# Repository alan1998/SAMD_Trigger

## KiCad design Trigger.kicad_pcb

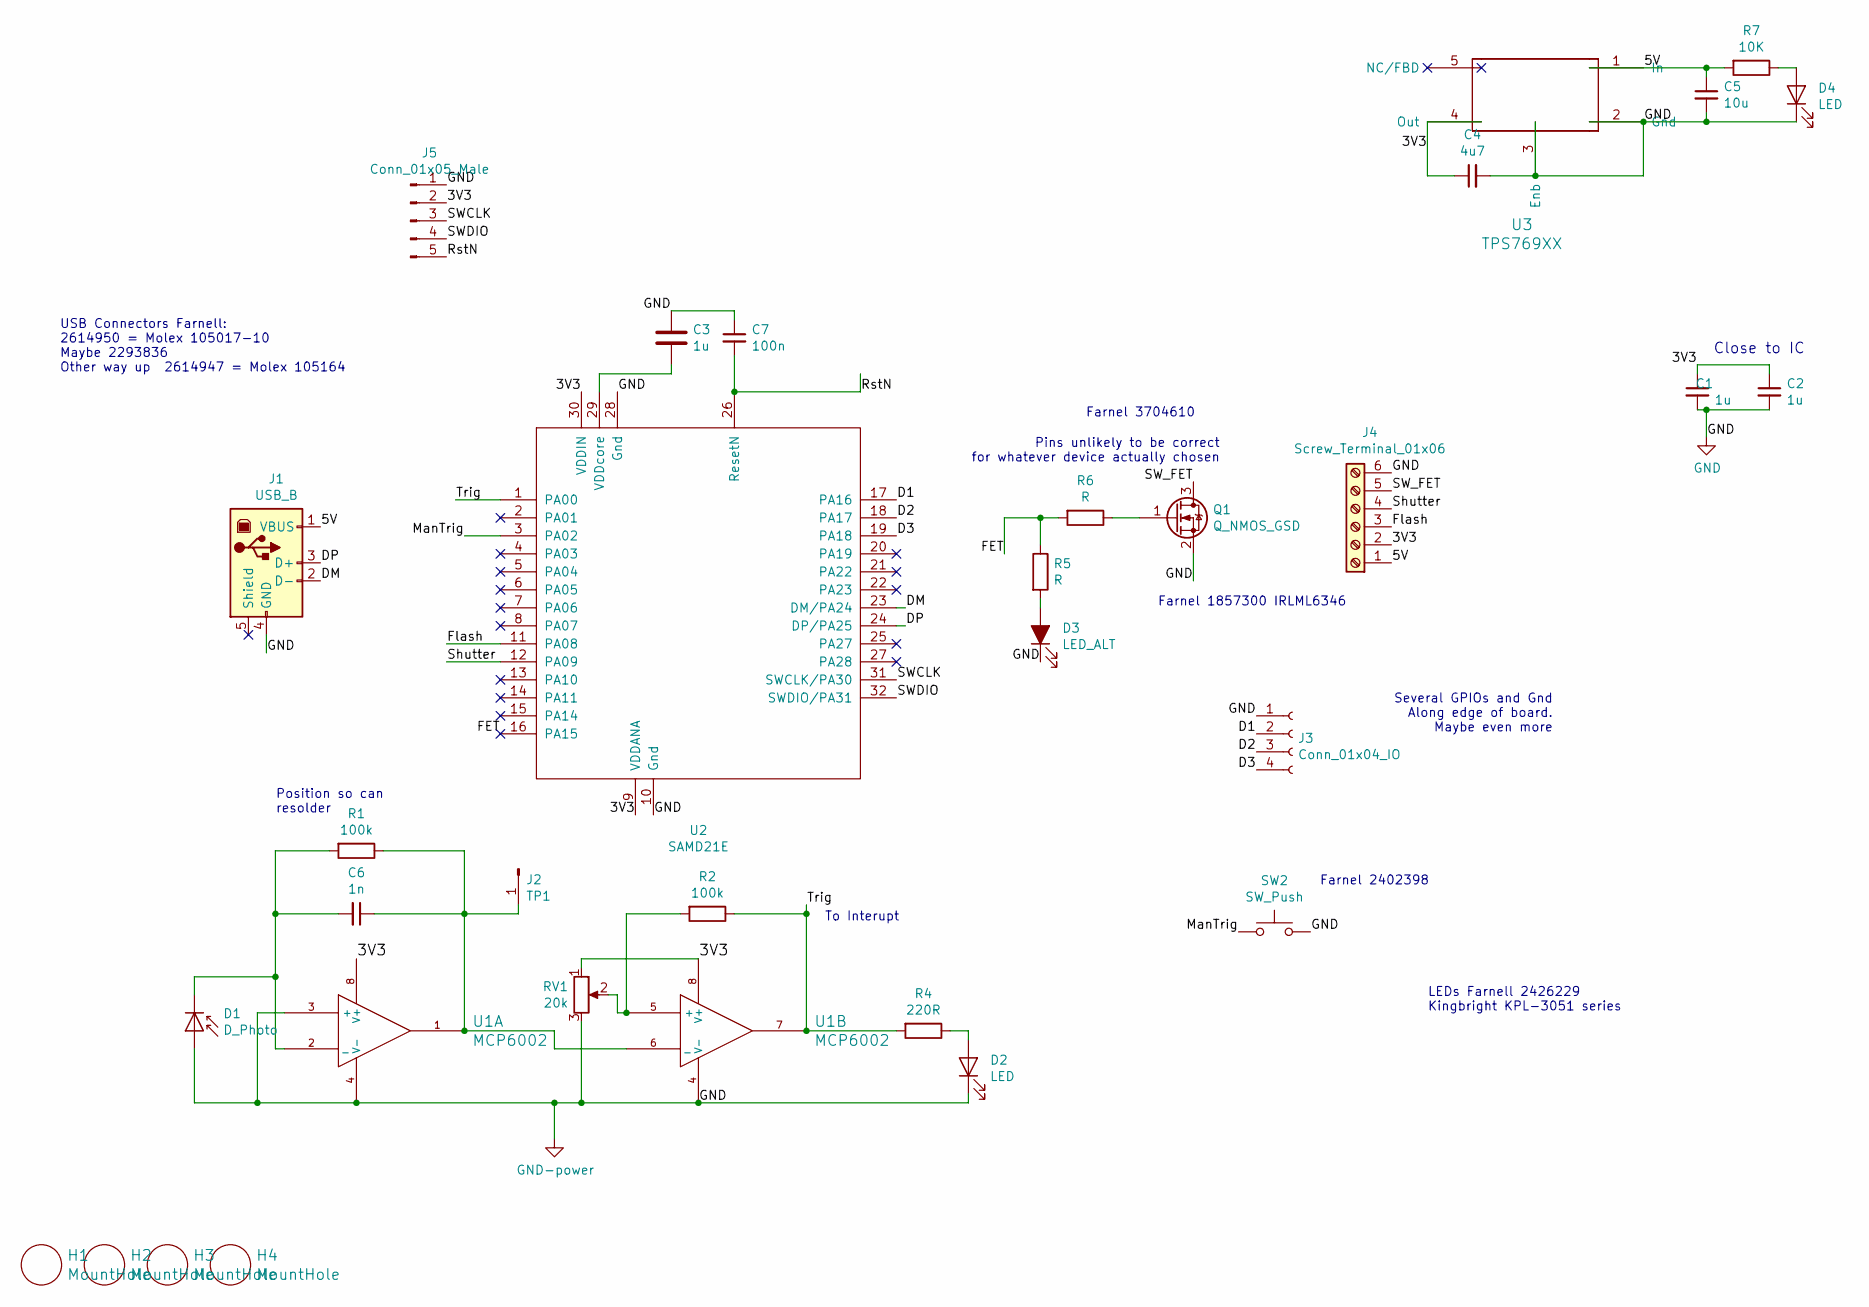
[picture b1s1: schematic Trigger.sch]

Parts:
C1, C2, C3: 1u; C_0805_HandSoldering
C4: 4u7; C_0805_HandSoldering
C5: 10u; C_0805_HandSoldering
C6: 1n; C_0805_HandSoldering
C7: 100n; C_0805_HandSoldering
D1: D_Photo; Pin_Header_Straight_1x02
D2, D4: LED; LED_SMD_3015
D3: LED_ALT; LED_SMD_3015
H1, H2, H3, H4: MountHole; 3mm_mount
J1: USB_B; USB_B_Micro_47346-0001
J2: TP1; Pin_Header_Angled_1x01
J3: Conn_01x04_IO; Pin_Header_Straight_1x04
J4: Screw_Terminal_01x06; Screw_6way_3_5mm
J5: Conn_01x05_Male; Pin_Header_Straight_1x05
Q1: Q_NMOS_GSD; SOT-23
R1: 100k; R_0805_HandSoldering
R2: 100k; R_0805
R4: 220R; R_0805
R5, R6: R; R_0805
R7: 10K; R_0805
RV1: 20k; Potentiometer_WirePads_largePads
SW2: SW_Push; Tact_SW
U1: MCP6002; SOIC-8-N
U2: SAMD21E; TQFP-32_7x7mm_Pitch0.8mm
U3: TPS769XX; SOT23_(DBV)

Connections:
/3V3: C1.1, C2.1, C4.1, J4.2, J5.2, RV1.1, U1.8 (V+), U2.9 (VDDANA), U2.30 (VDDIN), U3.4 (Out)
/5V: C5.1, J1.1 (VBUS), J4.1, R7.2, U3.1 (In)
/D1: J3.2, U2.17 (PA16)
/D2: J3.3, U2.18 (PA17)
/D3: J3.4, U2.19 (PA18)
/DM: J1.2 (D-), U2.23 (DM/PA24)
/DP: J1.3 (D+), U2.24 (DP/PA25)
/FET: R5.1, R6.2, U2.16 (PA15)
/Flash: J4.3, U2.11 (PA08)
/ManTrig: SW2.1, U2.3 (PA02)
/RstN: C7.2, J5.5, U2.26 (ResetN)
/SWCLK: J5.3, U2.31 (SWCLK/PA30)
/SWDIO: J5.4, U2.32 (SWDIO/PA31)
/SW_FET: J4.5, Q1.3 (D)
/Shutter: J4.4, U2.12 (PA09)
/Trig: R2.1, R4.2, U1.7, U2.1 (PA00)
GND: C1.2, C2.2, C3.1, C4.2, C5.2, C7.1, D1.2 (A), D2.1 (K), D3.1 (K), D4.1 (K), J1.4 (GND), J3.1, J4.6, J5.1, Q1.2 (S), RV1.3, SW2.2, U1.3 (+), U1.4 (V-), U2.10 (Gnd), U2.28 (Gnd), U3.2 (Gnd), U3.3 (Enb)
unnamed: C3.2, U2.29 (VDDcore)
unnamed: C6.1, J2.1, R1.1, U1.1, U1.6 (_)
unnamed: C6.2, D1.1 (K), R1.2, U1.2 (_)
unnamed: D2.2 (A), R4.1
unnamed: D3.2 (A), R5.2
unnamed: D4.2 (A), R7.1
unnamed: Q1.1 (G), R6.1
unnamed: R2.2, RV1.2, U1.5 (+)

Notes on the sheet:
Close to IC
USB Connectors Farnell: 2614950 = Molex 105017-10 Maybe 2293836 Other way up 2614947 = Molex 105164
Position so can resolder
To Interupt
Several GPIOs and Gnd Along edge of board. Maybe even more
Pins unlikely to be correct for whatever device actually chosen
LEDs Farnell 2426229 Kingbright KPL-3051 series
Farnel 3704610
Farnel 1857300 IRLML6346
Farnel 2402398

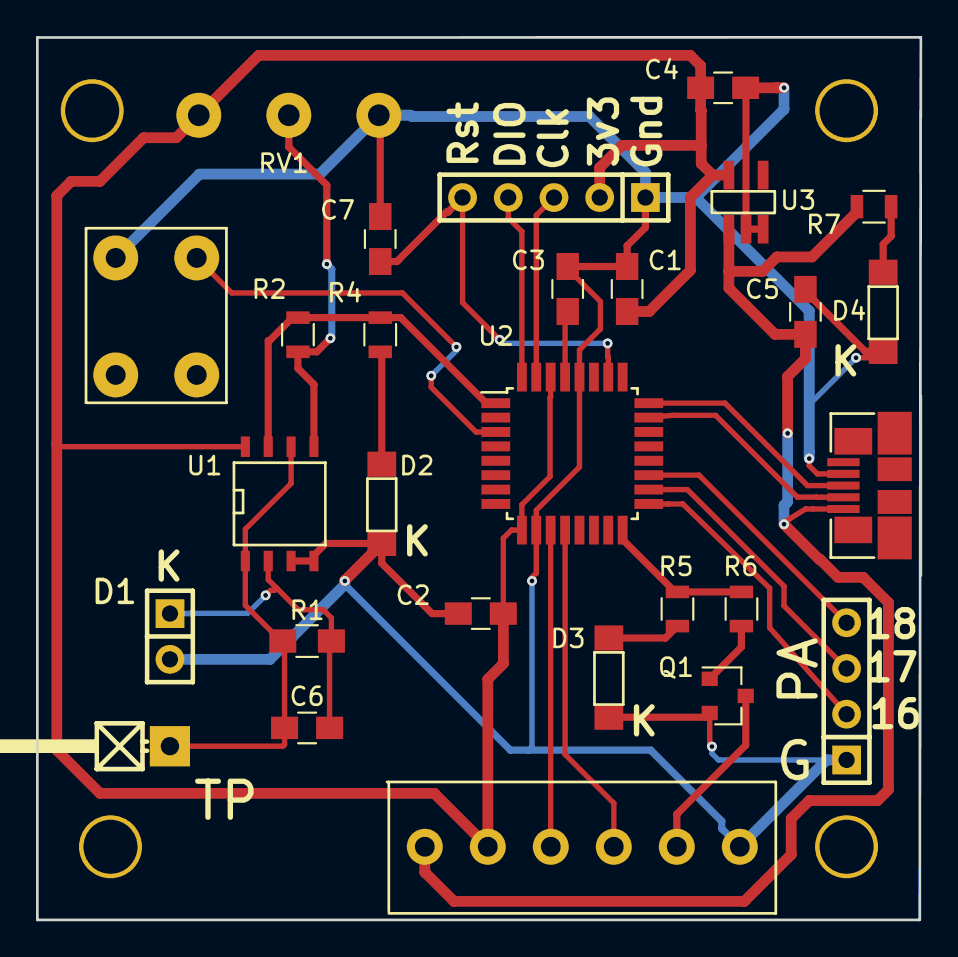
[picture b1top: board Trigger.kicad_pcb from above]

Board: 2 copper layers, 49.1 x 49.0 mm, 32 parts (0 on the bottom side), 25 nets.

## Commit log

2019-01-10 Initialise
2019-01-10 add lib
2019-01-10 more
2019-01-11 corrected symbol samd and more connections
2019-01-12 progress
2019-01-15 all connections made
2019-01-17 start parts list
2019-01-18 more footprints
2019-01-20 Finished parts list. Add 5pin header for debug
2019-01-21 Layout on board. Not in final positions
2019-01-22 Routed!
